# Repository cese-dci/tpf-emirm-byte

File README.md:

## Trabajo práctico final de la asignatura DCI ##
Este repositorio contiene el trabajo práctico final para la asignatura de Diseño de Circuitos Impresos de la carrera de posgrado de FIUBA.

* Autor: Emiliano Eduardo Rodriguez
* Título corto del trabajo:  USB To TTL Adaptaer Isolated
* Descripción: El circuito consiste en la realizaciòn de un puente USB a TTL con la salida TTL aislada para poder conectar placas bajo prueba que tienen fuentes de alimentaciòn no aislada.

## Licencia de este trabajo ##
Open Hardware License (OHL) 
https://www.oshwa.org/faq/

## Estructura del TP FINAL ##

Se propone y se pide utilizar la siguiente estructura.

* doc: Toda la información sobre el circuito, principalmente de autoría o procesamiento propio. Por ejemplo:
  * Notas de ingeniería propias.
  * Notas de aplicación propias.
  * Estudios previos, estado del arte, resumen de las investigaciones.
  * Notas con cálculos.
  * Dibujos adicionales.
  * Fotos de los prototipos.
  * Presupuestos, cotizaciones.
* info: Toda la iformación recolectada, principalmente de terceros, como por ejemplo:
  * Hojas de datos.
  * Notas de aplicación.
  * Info de productos comerciales.
  * Info en internet.
* pcb: Archivos de diseño esquemático y pcb.

Dependiendo la magnitud del proyecto, tendremos más o menos información en estos directorios. 
Revisar los README.md en cada directorio para conocer las pautas de cada uno para este TP.

NOTA: El alumno puede y debe borrar de este archivo todo lo que considere necesario, por ejemplo las aclaraciones del docente y esta misma nota.

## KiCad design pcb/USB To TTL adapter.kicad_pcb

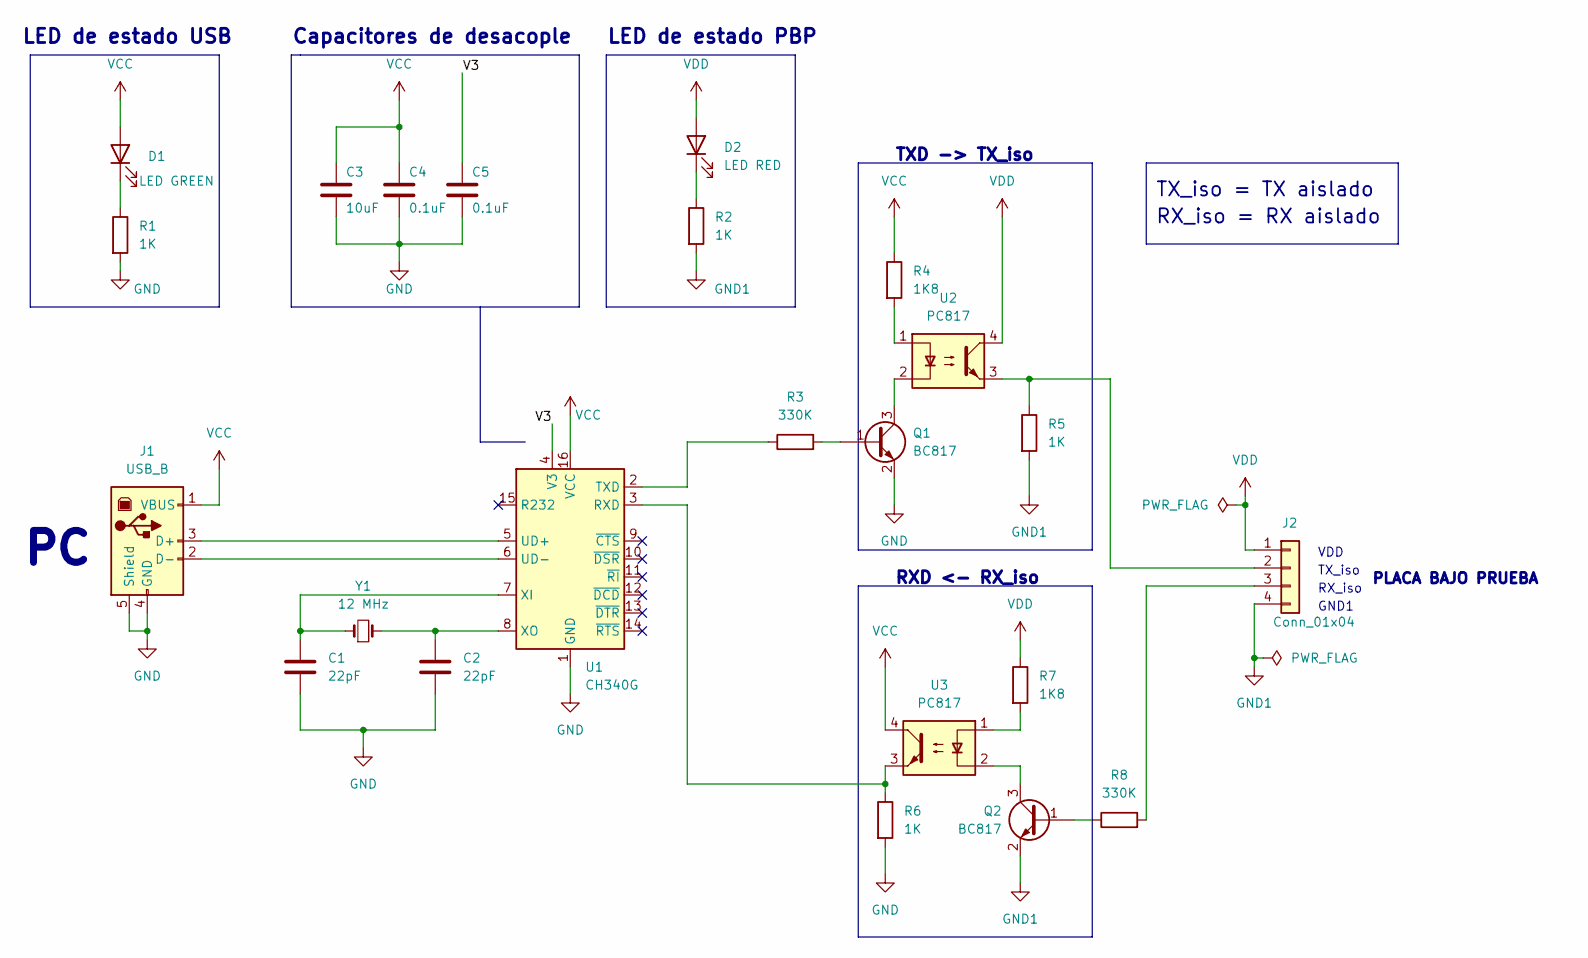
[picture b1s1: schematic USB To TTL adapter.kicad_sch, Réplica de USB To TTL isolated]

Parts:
C1, C2: 22pF; C_0805_2012Metric
C3: 10uF; C_0805_2012Metric
C4, C5: 0.1uF; C_0805_2012Metric
D1: LED GREEN; LED_0805_2012Metric
D2: LED RED; LED_0805_2012Metric
J1: USB_B; USB_B_Lumberg_2411_02_Horizontal
J2: Conn_01x04; PinHeader_1x04_P2.54mm_Vertical
Q1, Q2: BC817; SOT-23
R1, R2, R5, R6: 1K; R_0805_2012Metric
R3, R8: 330K; R_0805_2012Metric
R4, R7: 1K8; R_0805_2012Metric
U1: CH340G; SOIC-16_3.9x9.9mm_P1.27mm
U2, U3: PC817; DIP-4_W7.62mm_SMDSocket_SmallPads
Y1: 12 MHz; Crystal_HC49-4H_Vertical

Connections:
/V3: C5.1, U1.4 (V3)
GND: C1.2, C2.2, C3.2, C4.2, C5.2, J1.4 (GND), J1.5 (Shield), Q1.2 (E), R1.2, R6.2, U1.1 (GND)
GND1: J2.4, Q2.2 (E), R2.2, R5.2
unnamed: C1.1, U1.7 (XI), Y1.1
unnamed: C2.1, U1.8 (XO), Y1.2
unnamed: D1.1 (K), R1.1
unnamed: D2.1 (K), R2.1
unnamed: J1.2 (D-), U1.6 (UD-)
unnamed: J1.3 (D+), U1.5 (UD+)
unnamed: J2.2, R5.1, U2.3
unnamed: J2.3, R8.2
unnamed: Q1.1 (B), R3.2
unnamed: Q1.3 (C), U2.2
unnamed: Q2.1 (B), R8.1
unnamed: Q2.3 (C), U3.2
unnamed: R3.1, U1.2 (TXD)
unnamed: R4.2, U2.1
unnamed: R6.1, U1.3 (RXD), U3.3
unnamed: R7.2, U3.1
VCC: C3.1, C4.1, D1.2 (A), J1.1 (VBUS), R4.1, U1.16 (VCC), U3.4
VDD: D2.2 (A), J2.1, R7.1, U2.4

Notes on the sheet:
RX_iso = RX aislado
GND1
TX_iso = TX aislado
RX_iso
LED de estado USB
PLACA BAJO PRUEBA
TX_iso
TXD -> TX_iso
LED de estado PBP
RXD <- RX_iso
VDD
Capacitores de desacople

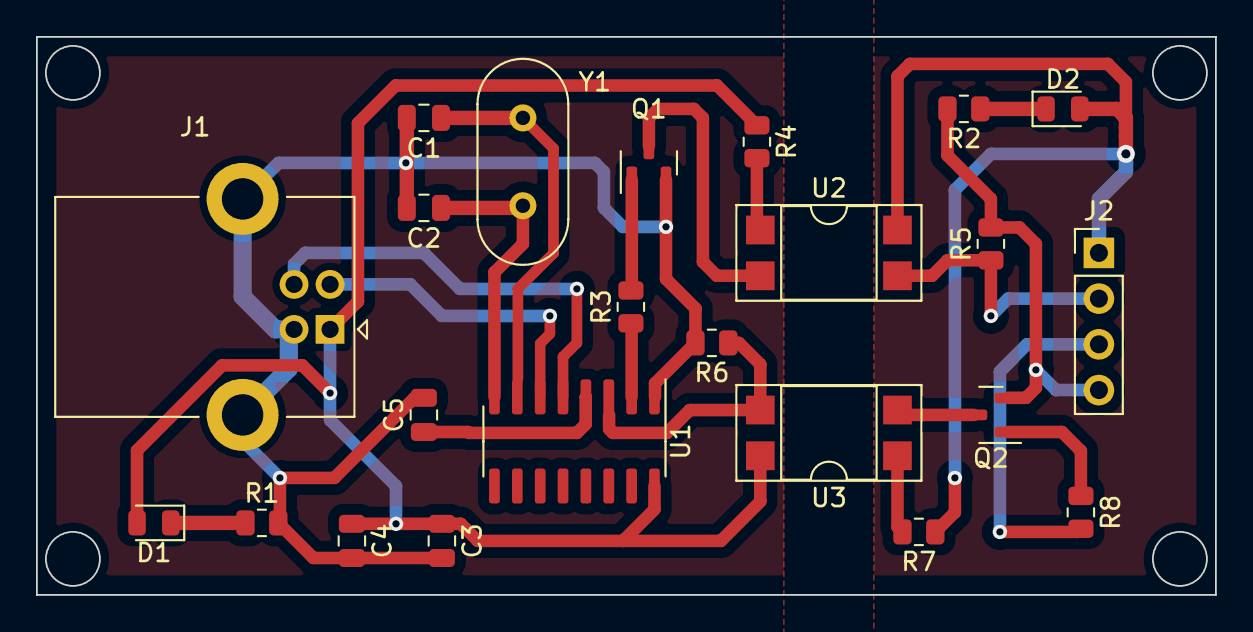
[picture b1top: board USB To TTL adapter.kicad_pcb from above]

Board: 2 copper layers, 65.5 x 31.0 mm, 23 parts (0 on the bottom side), 21 nets.

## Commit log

2022-07-28 first update
2022-07-29 add licence
2022-08-03 Update Schematic
2022-08-04 Update Schematic - PCB init
2022-08-18 Diseño de PCB
2022-08-18 update PCB
